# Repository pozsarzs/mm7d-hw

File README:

*** WARNING! It is not yet useable, because it is under development. WARNING ***

Short information
-----------------
MM7D * Air quality measuring device
Copyright (C) 2020 Pozsár Zsolt <pozsar.zsolt@szerafingomba.hu>
Homepage: <http://www.szerafingomba.hu/equipments/>

Documentation
 - version:             1.0
 - licence:             CC-BY-NC-4.0
 - language:            en

Hardware
 - version:             v200620
 - architecture:        xtensa
 - operation system:    -

Software
 - version:             v0.1
 - licence:             EUPL v1.1
 - language:            en

External libraries in package
 - Adafruit Unified Sensor v1.1.4 by Adafruit Industries
 - DHT sensor library v1.3.10 by Adafruit Industries

*** WARNING! It is not yet useable, because it is under development. WARNING ***

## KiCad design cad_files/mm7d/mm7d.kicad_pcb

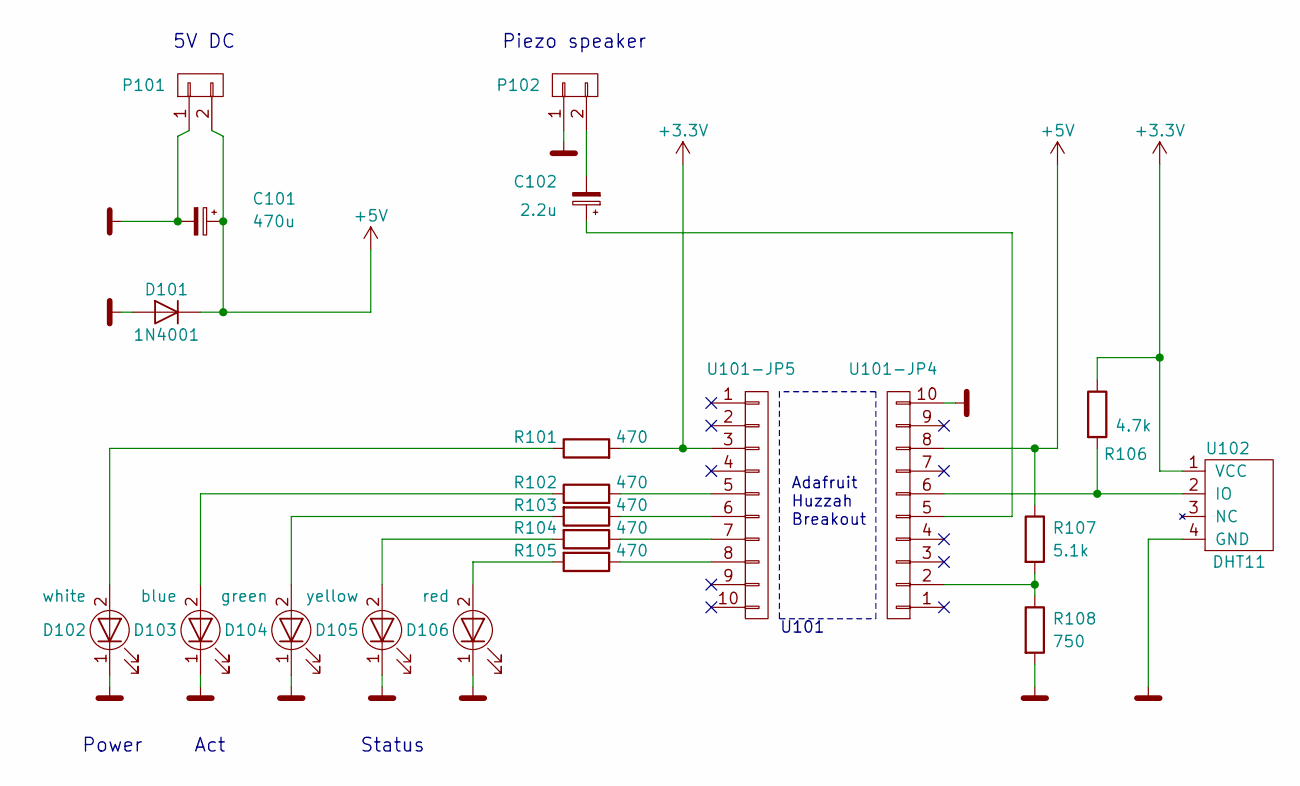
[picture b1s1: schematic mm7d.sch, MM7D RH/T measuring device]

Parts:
C101: 470u; C_Radial_D8_L11.5_P3.5
C102: 2.2u; C_Rect_L7_W4.5_P5
D101: 1N4001; Diode_DO-41_SOD81_Horizontal_RM10
D102: white; LED-3MM
D103: blue; LED-3MM
D104: green; LED-3MM
D105: yellow; LED-3MM
D106: red; LED-3MM
P101, P102: CONN_01X02; Socket_Strip_Straight_1x02
R101, R102, R103, R104, R105: 470; Resistor_Horizontal_RM7mm
R106: 4.7k; Resistor_Horizontal_RM7mm
R107: 5.1k; Resistor_Horizontal_RM10mm
R108: 750; Resistor_Horizontal_RM10mm
U101-JP4, U101-JP5: CONN_01X10; Socket_Strip_Straight_1x10
U102: DHT11; Socket_Strip_Straight_1x04

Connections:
+3V3: R101.2, R106.1, U101-JP5.3, U102.1 (VCC)
+5V: C101.1, D101.1 (K), P101.2, R107.1, U101-JP4.8
GND: C101.2, D101.2 (A), D102.1 (K), D103.1 (K), D104.1 (K), D105.1 (K), D106.1 (K), P101.1, P102.1, R108.2, U101-JP4.10, U102.4 (GND)
unnamed: C102.1, U101-JP4.5
unnamed: C102.2, P102.2
unnamed: D102.2 (A), R101.1
unnamed: D103.2 (A), R102.1
unnamed: D104.2 (A), R103.2
unnamed: D105.2 (A), R104.2
unnamed: D106.2 (A), R105.2
unnamed: R102.2, U101-JP5.5
unnamed: R103.1, U101-JP5.6
unnamed: R104.1, U101-JP5.7
unnamed: R105.1, U101-JP5.8
unnamed: R106.2, U101-JP4.6, U102.2 (IO)
unnamed: R107.2, R108.1, U101-JP4.2

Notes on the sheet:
Power Act Status
Adafruit Huzzah Breakout
U101
5V DC
Piezo speaker

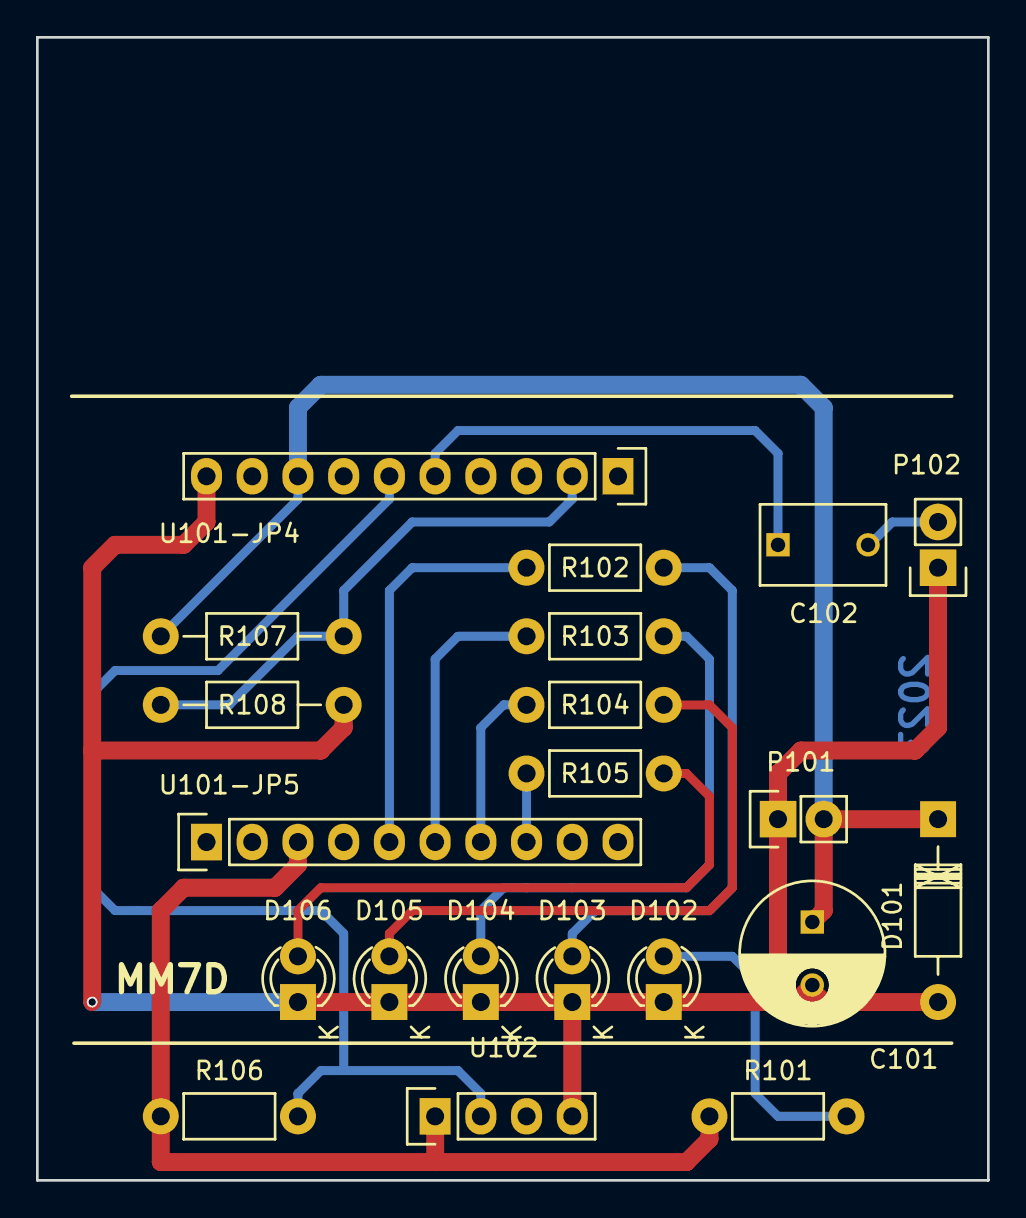
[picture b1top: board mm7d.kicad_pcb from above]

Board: 2 copper layers, 52.8 x 63.5 mm, 21 parts (0 on the bottom side), 16 nets.

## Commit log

2020-06-15 200615
2020-06-17 200617
2020-06-18 200618
2020-06-19 200619
2020-06-20 200620
2020-06-21 200621
2020-06-22 200622
2020-06-25 200625
2020-06-26 200626
2020-06-27 200627
2020-06-28 200628
2020-06-29 200629
2020-07-01 200701
2020-07-05 200705
2020-07-06 200706
2020-07-13 200713
2020-07-14 200714
2020-07-15 200715
2020-07-16 200716
2020-07-19 200719
2020-07-20 200720
2020-07-21 200721
2020-07-22 200722
2020-07-23 200723
2020-07-24 200724
2020-07-25 200725
2020-07-27 200727
2020-08-13 200813
2020-08-19 200819
2020-08-24 200824
2020-10-25 201025
2021-02-07 210207
2021-02-21 210221
2021-03-21 210321
2022-08-05 220805
2022-09-27 220927
2023-03-31 230331
2023-09-07 230907
2024-03-17 230317
2024-04-23 240423
2024-04-24 240424
